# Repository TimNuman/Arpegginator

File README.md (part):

# Arpegginator

Web prototype of a hardware MIDI step sequencer and arpeggiator. The end goal is a standalone device built around a **Teensy 4.1** (ARM Cortex-M7, 600MHz, 1MB RAM) driving a physical grid with RGB LEDs and a reflective memory LCD. This browser version serves as the development environment for the Rust engine -- the same code that runs here as WebAssembly will compile natively for the Teensy.

Place notes on an 8x16 grid, build chords, set up arpeggiation patterns, and send everything out over MIDI to your synths or DAW. The React UI simulates the hardware itself -- an enclosure at true scale carrying the button grid, the panel, the encoders and the transport keys, with host-only controls (tempo, MIDI ports) kept off the case as plain HTML while the Rust engine underneath handles all sequencer state and logic, keeping the path to hardware short.

## Features

### Sequencing

- 6 channels (4 melodic, 2 drum) with 8 patterns each
- Tick-based timing at 480 PPQN with zoom levels from 1/4 to 1/64 notes
- Per-note repeat system with configurable spacing
- Pattern loops with adjustable start point and length
- Pattern queuing with synchronized switching at loop boundaries
- Mute and solo per channel

### Chords and Arpeggios

- Stack notes in scale degrees (thirds, fourths, etc.) to build chords
- Multiple chord voicings per interval/size combination
- Inversions (infinite, up, down)
- Arpeggio styles: up, down, up-down, down-up, or all notes together
- Configurable arp voices (how many chord notes play simultaneously per step)

### Per-Repeat Modulation

Each note has 5 sub-mode arrays that cycle across repeats, each with its own loop behavior (reset, continue, or fill):

- **Velocity** -- per-repeat velocity values
- **Hit chance** -- probability that a repeat fires
- **Timing offset** -- micro-timing nudge as percentage of a step
- **Flam** -- grace note count per repeat
- **Modulate** -- pitch transposition in half steps

### Scales

- Notes are mapped through a configurable scale so the grid always stays in key
- Multiple scale types with root selection by circle of fifths
- Drum channels bypass the scale and map directly to GM MIDI notes

### Sound

- Built-in sounds -- no MIDI hardware needed. Drum channels play an analog-modeled 808 drum synth (kick, snare, clap, hats, toms/congas, cymbals, rimshot/claves, cowbell, maracas, mapped by GM drum note) rendered by the same Rust synth as everything else. Melodic channels play the Rust synth (`arp3-synth`): a polyphonic subtractive engine (selectable waveforms, sub osc, state-variable lowpass, ADSR, glide, drive) compiled to WASM and rendered in an AudioWorklet. Browsers without AudioWorklet fall back to a Web Audio kit and piano (works on e.g. iPad Safari).
- On the Teensy, the _same_ `arp3-synth` crate renders melodic channels through the i.MX RT1062's MQS (Medium Quality Sound) block -- 16-bit 44.1kHz stereo PWM on **pin 10 (right)** and **pin 12 (left)**, driven by a SAI3 FIFO interrupt. Hookup: a first-order RC low-pass per pin (e.g. 1kΩ series + 10nF to ground) into an amp or powered speakers; add a ~10µF DC-blocking cap in series with the output. No codec chip required.
- The Teensy also streams the synth over **USB audio**: the device enumerates as a 44.1kHz 16-bit stereo sound input (same USB audio function as the MIDI interface), so the synth can be monitored or recorded on the computer with no analog wiring at all. The USB stream is a bit-exact tap of what MQS plays.
- **Sound mode** -- per-channel patch editing on the grid (Ctrl + third bottom-row button). The left encoder cycles pages (preset picker, osc 1/2 waveform choosers that draw the wave in LEDs -- Shift+encoder on osc 2 nudges detune -- then amp with vol/mix/sub/glide faders, envelope, filter, FX), the right encoder edits the focused value (Shift for fine), and the grid is directly pressable: fader banks for continuous params, selector rows for waveforms. Edits are audible immediately while the sequencer runs.
- **Presets** -- the first Sound-mode page is a bank of 43 factory patches, color-coded by engine: classic-analog staples (FAT STACK, ACID LINE, RUBBER BASS, STARDUST, HOOVERCRAFT...), NES and SID chip flavors (8-BIT HERO, PIPE DREAM, COIN GET, BREADBIN, SEWER GOBLIN...), 4-op FM sounds (TINE MACHINE, CASTLE BELLS, MECHA BASS, RUST ORGAN...), lo-fi wavetables (OP WON, PHASE DANCER, TAPE GHOST...), additive patches (TONEWHEEL, BELL TOWER, GAMELAN...), and West Coast folder voices (EASEL RIDER, STEEL PAN, FOLD BLOOM, KALIMBA...). Tap a cell or step with the right encoder to load; editing any parameter marks the patch EDITED (amber) and lights a reset cell that restores the preset.
- **Wavefolder** -- a Buchla/Serge-style triangle folder in the shared back end, pre-filter: the FOLD knob (FX page on every engine) drives the signal up to 8x into reflecting boundaries, so harmonics bloom instead of clipping. Identity below unity, so fold 0 is bit-exact clean, and it's a mod-matrix target -- point a WHEEL lane at FOLD for the classic sweep. Drum channels get the same folder per instrument via a FOLD page after the kit chooser -- nine one-column faders (BD, SD, TOM, RS, CP, MA, CB, CY, HH) that draw the kit's fold spectrum on the grid, each press auditioning the drum it folds. Every voice folds against its own envelope, so hits strike folded and decay clean.
- **West Coast engine** -- a fifth synthesis engine built around that folder: a phase-aligned sine-to-triangle core (SHAPE) driven into the fold with adjustable symmetry (SYM offsets into asymmetric folding, DC-blocked) and envelope bloom (BLOOM makes fold depth ride the amp envelope -- strike bright, decay pure, the lowpass-gate gesture). Its FOLD page draws one cycle of the folded core live on the grid (the exact math the DSP runs) with a press-to-jump fold track on the bottom row; WEST holds the fold / shape / sym / bloom faders. The sub oscillator stays clean under the folded core. Presets: EASEL RIDER, STEEL PAN, FOLD BLOOM, WEST BRASS, GOLDEN GATE, KALIMBA (gold in the preset bank).
- **FM engine** -- a second synthesis engine in the style of ALM's Akemie's Castle / the Yamaha YM chips: 4 sine operators, the 8 classic YM2612 algorithms, quantized harmonic ratios (×0.5, ×1..×15), op-1 feedback, and a mod-envelope amount for FM plucks -- through the same sub osc, filter, and drive back end. Loading an FM preset swaps the Sound-mode pages to ALGO (the grid draws the operator routing; bottom row selects algorithms), OP (four ratio faders), and FM (depth / feedback / mod-env / detune faders). The engine follows the preset, so a channel switches engines just by picking a patch.
- **Wavetable engine** -- a third engine in the OP-1's lo-fi digital spirit: a morphing bank of 8 single-cycle tables (sine → triangle → saw → square → pulse → organ → formant → metal), CZ-style phase-distortion warp, and bit-crush with sample-rate decimation. Its WAVE page draws one cycle of the current morphed/warped wave live on the grid (the exact math the DSP runs) with a press-to-jump morph position track on the bottom row; DIGI holds the position / warp / crush / detune faders.
- **Additive engine** -- 16 sine partials with per-harmonic levels and a stretch (inharmonicity) control for bells and gamelan, with automatic muting of partials above Nyquist. Its HARM page turns the grid into a 16-column harmonic editor -- one one-wide fader per partial, draw your spectrum directly on the buttons -- and ADD holds the stretch fader. Presets: TONEWHEEL, GLASS HARP, BELL TOWER, PAN PIPE, BUZZ MACHINE, GAMELAN (rose in the preset bank).
- **808 drum synth** -- an analog-modeled TR-808 kit in the spirit of Tiptop Audio's 808 module line (BD808, SD808, RS808, CP808, MA808, CB808, HH808, CY808 and the tom/conga voices), synthesized in `arp3-synth` from the classic circuit recipes: bridged-T swept sines for kick and toms, dual body sines + snappy noise for the snare, the 6-square Schmitt bank for hats and cymbal (one hi-hat voice, so a closed hat chokes an open one, as on the hardware), the two famous 540/800 Hz squares for the cowbell, and the 3-burst envelope for the clap. Sound mode on a drum channel opens a KIT chooser page followed by one page per instrument -- BD, SD, TOMS, RIM/CLAVE, CLAP, MARACAS, COWBELL, CYMBAL, HI-HAT -- each a fader bank of that module's front-panel knobs (tune / tone / decay / snappy / level, CH+OH decays on the hat page) plus an audition pad in the bottom-right corner (Shift auditions the open hat). Edits stream to the synth live and apply to already-ringing hits.
- **FM drum synth** -- a second kit engine, selectable per channel on the KIT page: a 2-operator phase-modulation kit in the YM-chip / Machinedrum-EFM spirit. Each instrument keeps its page but swaps in an FM knob driving a modulator with its own fast decay -- ratio-1 growl on the kick, an inharmonic x2.43 body on the snare, high-ratio metallic rings for rimshot and cowbell, and a two-stage modulator stack (x5.42 -> x3.52 -> carrier) for the DX-metal cymbal and hats (choke behavior intact). Each kit keeps its own parameter bank, so switching engines never loses knob settings, and a ringing voice finishes on the kit it was struck with.
- **Drum sampler** -- after the instrument pages, the same left-encoder cycle reaches the sampler: 16 sample slots mapped to the GM drum notes (slot 1 = kick 35/36, and so on), so recorded samples replace the 808 recipes note-by-note while empty slots keep the synthesized kit. Five pages: **SLOT** (rows are slots, mirroring the drum lanes -- each loaded row draws its take's waveform across the columns, press a row to select and audition it, Shift+press to snap a pitched sample to the scale root using its auto-detected key), **REC** (arm, record from the browser mic with threshold trigger, pre-roll, and a live scrolling waveform + level meter -- red is reserved for recording), **TRIM** (start/end handles on a press-to-jump track, edits replay the cut), **PLAY** (speed / pitch / level / decay faders, ONE / LOOP / GATE modes, and a GRAIN/TAPE toggle -- granular playback keeps speed and pitch fully independent, TAPE links them as varispeed), and **MOD** (per-slot filter cutoff / resonance / drive). Takes are normalized, key-tagged (YIN pitch detection), and rendered by the same `arp3-synth` crate that will play them from PSRAM on the Teensy, where recording will come from the codec line-in.
- Sends note-on/off to any connected MIDI device via Web MIDI API
- Receives MIDI clock for external sync (start, stop, continue, tempo detection)
- Device selections persist across sessions

### Display

- Simulated **320x240 memory LCD** showing note parameters, chord names, voicings, and playback state -- rendered entirely in Rust and blitted to a canvas via an RGB565 framebuffer, then mapped through a panel simulation so the browser shows what the panel shows. The target panel is a **JDI LPM044M141A**: 4.4", 320x240 over an 89.66 x 67.25 mm active area, reflective, no backlight, and 1 bit per channel. At 0.28 mm per pixel it is coarse enough that the UI is physically large -- a value in Spleen 8x16 stands 2.8 mm tall -- so the design is built for what that panel can show rather than ported onto it.
- **Paper UI** -- white ground, black ink, and no tone in between. There is no grey to dim a label with, so hierarchy comes from size (Spleen 5x8 labels against 8x16 values) and emphasis comes from inversion or a filled slab. Shading is a 4x4 ordered dither, used for areas only -- fader tracks and inactive slots -- never for glyphs or hairlines.
- **Color means live state, never structure.** The only colored pixels on screen are the three modifier buttons along the bottom edge -- blue for the grid, yellow for up/down, magenta for left/right -- plus whichever field the held modifier is currently pointing at, which takes that same color as its well fill. Everything else is black and white. Because color is redundant with the icons and inversion already there, the UI stays complete on a monochrome panel.
- **Bitmap fonts** -- Spleen (BSD-2), parsed straight from BDF at build time into packed 1-bit glyphs. A vector face rasterized at 11px puts stems on fractional coordinates at ~50% coverage, and a 1-bit threshold rounds them away, so `CH` renders as `CII`. Spleen is drawn on the pixel grid, so there is nothing to threshold. The four-size ladder is roughly 12 kB of glyph data against ~175 kB of anti-aliased coverage bytes.
- Color-coded channels on the grid with visual flags for playhead, beat markers, loop boundaries, and selected notes

## Architecture

```
┌─────────────────────────────────────────────────┐
│  React UI (TypeScript)                          │
│  Grid, ButtonGrid, TouchStrip, panel canvas     │
├──────────────┬──────────────────────────────────┤
│  WasmEngine  │  Actions / Playback loop         │
│  (JS<>Rust)  │  (tick scheduling, BPM)          │
├──────────────┴──────────────────────────────────┤
│  Rust Engine (wasm32 / ARM Cortex-M7)           │
│  Pattern storage, playback tick processing,     │
│  grid computation, input handling, OLED         │
├─────────────────────────────────────────────────┤
│  Platform layer (cfg-switched per target)       │
│  WASM: JS callbacks | Teensy: hardware MIDI     │
├─────────────────────────────────────────────────┤
│  Web MIDI API (browser) / USB MIDI (Teensy)     │
└─────────────────────────────────────────────────┘
```

The Rust engine is the single source of truth for all sequencer state. In the browser, React reads grid buffers and UI state directly from WASM linear memory on each render. The JS side owns the transport timer loop (1ms `setTimeout`) and MIDI I/O. On Teensy, the engine runs natively at 600MHz with hardware MIDI output.

### Platform Abstraction

The engine uses `#[cfg(target_arch)]` to switch between platform backends:

- **wasm32** -- calls JS imports via `extern "C"` for MIDI output and UI callbacks
- **arm** -- (planned) direct hardware MIDI and GPIO for Teensy 4.1
- **test** -- no-op stubs for unit testing

### Teensy 4.1 Constraints

The engine is designed to fit within the Teensy's 1MB RAM budget:

- All state lives in fixed-size arrays (no heap allocation required)
- Pool allocators for NoteEvents (1024 slots) and SubModeArrays (512 slots) with graceful degradation on exhaustion
- `f32` only (Cortex-M7 has hardware FPU for single-precision, not double)
- Optimized alpha blending with bitshift instead of division

## Controls

The grid maps to your keyboard like a controller:

```
Row 4:  1 2 3 4 5 6 7 8
Row 5:  Q W E R T Y U I
Row 6:  A S D F G H J K
Row 7:  Z X C V B N M ,
```

Other keys:

- **Space** -- play / stop
- **Arrow keys** -- navigate (with modifiers for mode-specific actions)
- **Backspace** -- deselect / reset
- **Delete** -- delete selected note
- **[ / ]** -- zoom out / in
- **Shift, Ctrl, Alt, Cmd** -- modifier keys for extended actions (shown in the UI)

The grid also responds to mouse clicks and touch input with drag support.

## Prerequisites

- [Node.js](https://nodejs.org/) (v18+)
- [Rust](https://www.rust-lang.org/tools/install) with the `wasm32-unknown-unknown` target (`rustup target add wasm32-unknown-unknown`)
- Any modern browser. Built-in sounds work everywhere; MIDI output/sync additionally requires [Web MIDI API](https://developer.mozilla.org/en-US/docs/Web/API/Web_MIDI_API) support (Chrome, Edge, Opera)

## Getting Started

```bash
# Install dependencies
npm install

# Build the WASM engine (requires Rust + wasm32-unknown-unknown target)
npm run build:wasm

# Start the dev server
npm run dev
```

Open the app and press play -- built-in 808 + piano sounds work out of the box. To drive external gear instead, pick a MIDI output device in the Out selector in the page's top-right corner (Chrome will prompt for MIDI access).

## Build

```bash
# Full production build (WASM + TypeScript + Vite)
npm run build

# WASM only
npm run build:wasm

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
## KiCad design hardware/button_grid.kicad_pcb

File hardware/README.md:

# 16×8 Button Grid PCB

KiCad PCB for the Arpegginator's main button grid: 128 Kailh Choc v1
low-profile switches with per-key RGBW LEDs and anti-ghosting diodes.

## Specs

| Parameter        | Value                                       |
| ---------------- | ------------------------------------------- |
| Grid             | 16 columns × 8 rows (128 keys)              |
| Switch           | Kailh Choc v1 (PG1350), through-hole        |
| LED              | SK6812MINI-E RGBW (3535), addressable chain |
| Anti-ghost diode | 1N4148W (SOD-323), one per switch           |
| Scanning         | 16 column + 8 row GPIO pins (24 total)      |
| LED data         | 1 GPIO pin (serial chain, 128 LEDs)         |
| Key spacing      | 19.05 mm (standard 1U)                      |
| Board size       | ~320 × 172 mm                               |
| Layers           | 2 (F.Cu + B.Cu)                             |

## Matrix Wiring

Each key cell:

```
COL pin ──── SW pad 1 ─┤ switch ├── SW pad 2 ──── Diode anode ─┤►├── Diode cathode ──── ROW pin
```

The 1N4148W diode on each switch prevents ghosting when multiple keys are
pressed simultaneously. Cathode connects to the row line, anode to the switch.

Scanning: drive one column LOW at a time, read all 8 rows. A pressed key
pulls its row LOW through the diode.

## LED Chain

SK6812MINI-E LEDs are daisy-chained in a snaking pattern:

```
Row 0:  LED1 → LED2 → ... → LED16    (left to right)
Row 1:  LED17 ← LED18 ← ... ← LED32  (right to left)
Row 2:  LED33 → LED34 → ... → LED48   (left to right)
  ...etc...
```

This minimizes routing distance for the data line. One GPIO pin (LED_DIN)
drives the entire chain.

## Connectors

- **J1** (20-pin header): COL0–COL15, VCC, GND, LED_DIN, spare
- **J2** (8-pin header): ROW0–ROW7

Both at the bottom edge, 2.54 mm pitch.

## Teensy 4.1 Pin Mapping (suggested)

| Function   | Teensy Pins      | Count |
| ---------- | ---------------- | ----- |
| COL0–COL15 | 0–9, 10–15       | 16    |
| ROW0–ROW7  | 16–17, 20–25     | 8     |
| LED_DIN    | 26 (or any GPIO) | 1     |
| VCC        | 3.3V             | 1     |
| GND        | GND              | 1     |

## Generating the PCB

```bash
python3 generate_pcb.py
```

This writes `button_grid.kicad_pcb` and `bom.md` next to the script. The
script emits a KiCad 10 (format `20260206`) file and then runs
`kicad-cli pcb upgrade --force` on it so the output matches KiCad's exact
canonical serialization — regenerations produce clean, readable diffs
against revisions saved from the KiCad GUI. Requires KiCad 10 with
`kicad-cli` on `PATH` (or installed at the default macOS location); without
it the PCB is still valid but stays in compact form until first opened and
saved in KiCad.

All geometry is parameterized at the top of the script. Adjust `PITCH`,
`MARGIN`, switch footprint offsets, etc. as needed then regenerate.

## Trace Routing (fully routed)

The generated PCB includes complete trace routing (1117 traces, 639 vias):

**F.Cu (front copper):**

- **Column buses**: Vertical trunk at 2.5 mm left of switch center (dodges
  the 3 mm center post), with horizontal stubs to each switch pad 1
- **Switch→diode**: Short vertical trace from switch pad 2 to diode anode

**B.Cu (back copper):**

- **Row buses**: Horizontal traces connecting all 16 diode cathodes per row,
  via at each diode cathode to drop from F.Cu to B.Cu
- **LED data chain**: Horizontal channel at cy−2.0 mm for intra-row
  connections; inter-row connections route through the board margins
  (left for odd→even, right for even→odd transitions)
- **LED VCC bus**: Horizontal power trace (0.5 mm) per row at cy−4.5 mm,
  via at each LED VCC pad with short stub to the bus
- **GND fill**: Full board ground pour, auto-clearance around all other nets

**LED GND**: Via at each LED GND pad connects directly to the B.Cu ground fill.

**Not routed**: Connector fan-out from grid to J1/J2. The column and row buses
are fully connected within the grid, but the last-mile routing to the pin
headers depends on your physical connector choice. Route these manually in KiCad
or replace J1/J2 with direct wiring pads.

## Bill of Materials

| Ref      | Part            | Package | Qty | Notes                   |
| -------- | --------------- | ------- | --- | ----------------------- |
| SW1–128  | Kailh Choc v1   | PG1350  | 128 | Low-profile mech switch |
| D1–128   | 1N4148W         | SOD-323 | 128 | Anti-ghosting diode     |
| LED1–128 | SK6812MINI-E    | 3535    | 128 | RGBW addressable LED    |
| J1       | Pin header 1×20 | 2.54 mm | 1   | Columns + power + LED   |
| J2       | Pin header 1×8  | 2.54 mm | 1   | Rows                    |

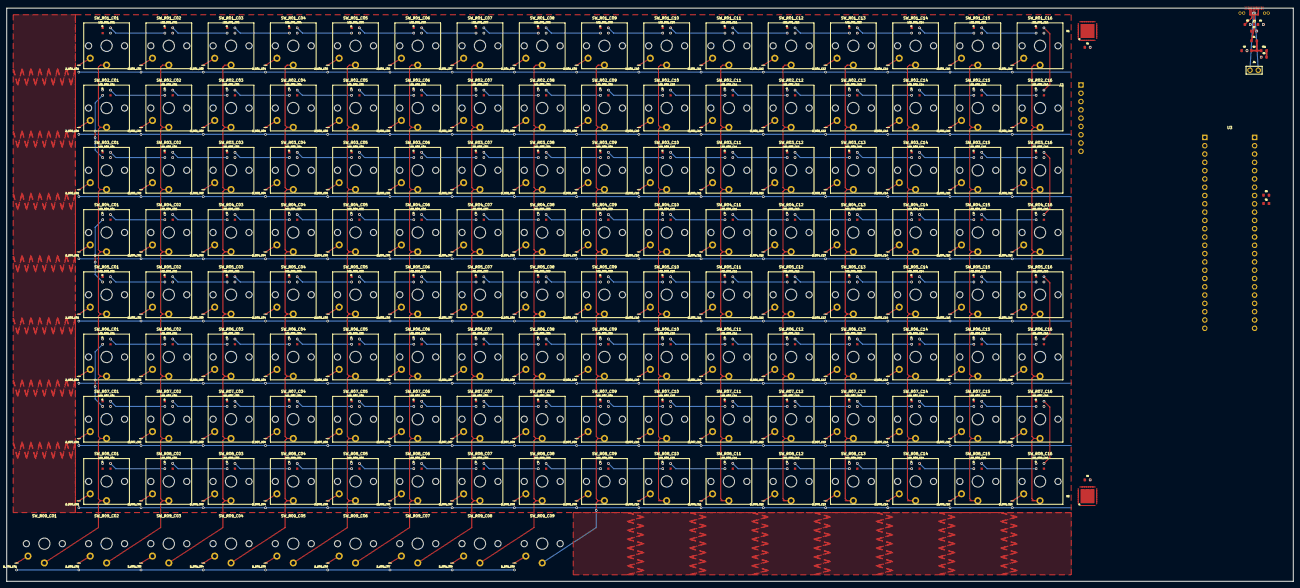
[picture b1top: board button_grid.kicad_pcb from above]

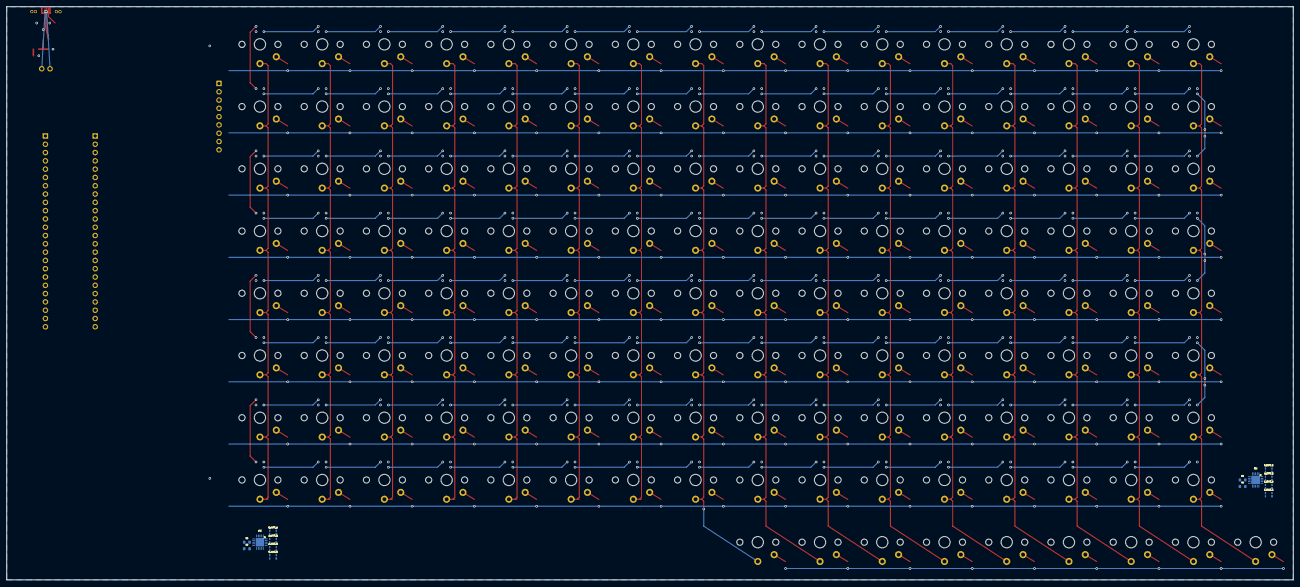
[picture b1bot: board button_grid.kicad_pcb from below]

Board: 2 copper layers, 393.9 x 175.4 mm, 434 parts (14 on the bottom side), 325 nets.

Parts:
C1, C2, C4, C5, C5#2, C6: 100nF; C_0603
C7, C9: 10uF; C_0603
C8: 100uF; C_0603
D_R01_C01, D_R01_C02, D_R01_C03, D_R01_C04, D_R01_C05, D_R01_C06, D_R01_C07, D_R01_C08, D_R01_C09, D_R01_C10, D_R01_C11, D_R01_C12, D_R01_C13, D_R01_C14, D_R01_C15, D_R01_C16, D_R02_C01, D_R02_C02, D_R02_C03, D_R02_C04, D_R02_C05, D_R02_C06, D_R02_C07, D_R02_C08, D_R02_C09, D_R02_C10, D_R02_C11, D_R02_C12, D_R02_C13, D_R02_C14, D_R02_C15, D_R02_C16, D_R03_C01, D_R03_C02, D_R03_C03, D_R03_C04, D_R03_C05, D_R03_C06, D_R03_C07, D_R03_C08, D_R03_C09, D_R03_C10, D_R03_C11, D_R03_C12, D_R03_C13, D_R03_C14, D_R03_C15, D_R03_C16, D_R04_C01, D_R04_C02, D_R04_C03, D_R04_C04, D_R04_C05, D_R04_C06, D_R04_C07, D_R04_C08, D_R04_C09, D_R04_C10, D_R04_C11, D_R04_C12, D_R04_C13, D_R04_C14, D_R04_C15, D_R04_C16, D_R05_C01, D_R05_C02, D_R05_C03, D_R05_C04, D_R05_C05, D_R05_C06, D_R05_C07, D_R05_C08, D_R05_C09, D_R05_C10, D_R05_C11, D_R05_C12, D_R05_C13, D_R05_C14, D_R05_C15, D_R05_C16, D_R06_C01, D_R06_C02, D_R06_C03, D_R06_C04, D_R06_C05, D_R06_C06, D_R06_C07, D_R06_C08, D_R06_C09, D_R06_C10, D_R06_C11, D_R06_C12, D_R06_C13, D_R06_C14, D_R06_C15, D_R06_C16, D_R07_C01, D_R07_C02, D_R07_C03, D_R07_C04, D_R07_C05, D_R07_C06, D_R07_C07, D_R07_C08, D_R07_C09, D_R07_C10, D_R07_C11, D_R07_C12, D_R07_C13, D_R07_C14, D_R07_C15, D_R07_C16, D_R08_C01, D_R08_C02, D_R08_C03, D_R08_C04, D_R08_C05, D_R08_C06, D_R08_C07, D_R08_C08, D_R08_C09, D_R08_C10, D_R08_C11, D_R08_C12, D_R08_C13, D_R08_C14, D_R08_C15, D_R08_C16: 1N4148W; D_SOD-323
D_R09_C01, D_R09_C02, D_R09_C03, D_R09_C04, D_R09_C05, D_R09_C06, D_R09_C07, D_R09_C08, D_R09_C09: D_SOD-323
D_TVS3_0, D_TVS3_1, D_TVS3_2, D_TVS3_3, D_TVS4_0, D_TVS4_1, D_TVS4_2, D_TVS4_3: PRTR5V0U2X; PRTR5V0U2X_SOT-143B
F1: 2A PTC; R_0603
FB1: 600R@100MHz; R_0603
J2: TFT 2.4in; ILI9341_2.4inch
J3: USB-C; USB_C_Mid_Mount
J4: USB D+/D-; USB_Dev_Pads
LED_R01_C01, LED_R01_C02, LED_R01_C03, LED_R01_C04, LED_R01_C05, LED_R01_C06, LED_R01_C07, LED_R01_C08, LED_R01_C09, LED_R01_C10, LED_R01_C11, LED_R01_C12, LED_R01_C13, LED_R01_C14, LED_R01_C15, LED_R01_C16, LED_R02_C01, LED_R02_C02, LED_R02_C03, LED_R02_C04, LED_R02_C05, LED_R02_C06, LED_R02_C07, LED_R02_C08, LED_R02_C09, LED_R02_C10, LED_R02_C11, LED_R02_C12, LED_R02_C13, LED_R02_C14, LED_R02_C15, LED_R02_C16, LED_R03_C01, LED_R03_C02, LED_R03_C03, LED_R03_C04, LED_R03_C05, LED_R03_C06, LED_R03_C07, LED_R03_C08, LED_R03_C09, LED_R03_C10, LED_R03_C11, LED_R03_C12, LED_R03_C13, LED_R03_C14, LED_R03_C15, LED_R03_C16, LED_R04_C01, LED_R04_C02, LED_R04_C03, LED_R04_C04, LED_R04_C05, LED_R04_C06, LED_R04_C07, LED_R04_C08, LED_R04_C09, LED_R04_C10, LED_R04_C11, LED_R04_C12, LED_R04_C13, LED_R04_C14, LED_R04_C15, LED_R04_C16, LED_R05_C01, LED_R05_C02, LED_R05_C03, LED_R05_C04, LED_R05_C05, LED_R05_C06, LED_R05_C07, LED_R05_C08, LED_R05_C09, LED_R05_C10, LED_R05_C11, LED_R05_C12, LED_R05_C13, LED_R05_C14, LED_R05_C15, LED_R05_C16, LED_R06_C01, LED_R06_C02, LED_R06_C03, LED_R06_C04, LED_R06_C05, LED_R06_C06, LED_R06_C07, LED_R06_C08, LED_R06_C09, LED_R06_C10, LED_R06_C11, LED_R06_C12, LED_R06_C13, LED_R06_C14, LED_R06_C15, LED_R06_C16, LED_R07_C01, LED_R07_C02, LED_R07_C03, LED_R07_C04, LED_R07_C05, LED_R07_C06, LED_R07_C07, LED_R07_C08, LED_R07_C09, LED_R07_C10, LED_R07_C11, LED_R07_C12, LED_R07_C13, LED_R07_C14, LED_R07_C15, LED_R07_C16, LED_R08_C01, LED_R08_C02, LED_R08_C03, LED_R08_C04, LED_R08_C05, LED_R08_C06, LED_R08_C07, LED_R08_C08, LED_R08_C09, LED_R08_C10, LED_R08_C11, LED_R08_C12, LED_R08_C13, LED_R08_C14, LED_R08_C15, LED_R08_C16: SK6812MINI-E
R1, R2: 4.7k; R_0603
R3, R4: 5.1k; R_0603
R5: 0R; R_0603
SW_R01_C01, SW_R01_C02, SW_R01_C03, SW_R01_C04, SW_R01_C05, SW_R01_C06, SW_R01_C07, SW_R01_C08, SW_R01_C09, SW_R01_C10, SW_R01_C11, SW_R01_C12, SW_R01_C13, SW_R01_C14, SW_R01_C15, SW_R01_C16, SW_R02_C01, SW_R02_C02, SW_R02_C03, SW_R02_C04, SW_R02_C05, SW_R02_C06, SW_R02_C07, SW_R02_C08, SW_R02_C09, SW_R02_C10, SW_R02_C11, SW_R02_C12, SW_R02_C13, SW_R02_C14, SW_R02_C15, SW_R02_C16, SW_R03_C01, SW_R03_C02, SW_R03_C03, SW_R03_C04, SW_R03_C05, SW_R03_C06, SW_R03_C07, SW_R03_C08, SW_R03_C09, SW_R03_C10, SW_R03_C11, SW_R03_C12, SW_R03_C13, SW_R03_C14, SW_R03_C15, SW_R03_C16, SW_R04_C01, SW_R04_C02, SW_R04_C03, SW_R04_C04, SW_R04_C05, SW_R04_C06, SW_R04_C07, SW_R04_C08, SW_R04_C09, SW_R04_C10, SW_R04_C11, SW_R04_C12, SW_R04_C13, SW_R04_C14, SW_R04_C15, SW_R04_C16, SW_R05_C01, SW_R05_C02, SW_R05_C03, SW_R05_C04, SW_R05_C05, SW_R05_C06, SW_R05_C07, SW_R05_C08, SW_R05_C09, SW_R05_C10, SW_R05_C11, SW_R05_C12, SW_R05_C13, SW_R05_C14, SW_R05_C15, SW_R05_C16, SW_R06_C01, SW_R06_C02, SW_R06_C03, SW_R06_C04, SW_R06_C05, SW_R06_C06, SW_R06_C07, SW_R06_C08, SW_R06_C09, SW_R06_C10, SW_R06_C11, SW_R06_C12, SW_R06_C13, SW_R06_C14, SW_R06_C15, SW_R06_C16, SW_R07_C01, SW_R07_C02, SW_R07_C03, SW_R07_C04, SW_R07_C05, SW_R07_C06, SW_R07_C07, SW_R07_C08, SW_R07_C09, SW_R07_C10, SW_R07_C11, SW_R07_C12, SW_R07_C13, SW_R07_C14, SW_R07_C15, SW_R07_C16, SW_R08_C01, SW_R08_C02, SW_R08_C03, SW_R08_C04, SW_R08_C05, SW_R08_C06, SW_R08_C07, SW_R08_C08, SW_R08_C09, SW_R08_C10, SW_R08_C11, SW_R08_C12, SW_R08_C13, SW_R08_C14, SW_R08_C15, SW_R08_C16: PG1350; Kailh_Choc_V1
SW_R09_C01, SW_R09_C02, SW_R09_C03, SW_R09_C04, SW_R09_C05, SW_R09_C06, SW_R09_C07, SW_R09_C08, SW_R09_C09: Kailh_Choc_V1
U1, U2: MCP23S17; MCP23S17_QFN28
U3: Teensy 4.1; Teensy41
U3#2, U4: MPR121; MPR121_QFN20

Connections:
COL0: SW_R01_C01.1, SW_R02_C01.1, SW_R03_C01.1, SW_R04_C01.1, SW_R05_C01.1, SW_R06_C01.1, SW_R07_C01.1, SW_R08_C01.1, SW_R09_C01.1, U1.21
COL1: SW_R01_C02.1, SW_R02_C02.1, SW_R03_C02.1, SW_R04_C02.1, SW_R05_C02.1, SW_R06_C02.1, SW_R07_C02.1, SW_R08_C02.1, SW_R09_C02.1, U1.22
COL2: SW_R01_C03.1, SW_R02_C03.1, SW_R03_C03.1, SW_R04_C03.1, SW_R05_C03.1, SW_R06_C03.1, SW_R07_C03.1, SW_R08_C03.1, SW_R09_C03.1, U1.23
COL3: SW_R01_C04.1, SW_R02_C04.1, SW_R03_C04.1, SW_R04_C04.1, SW_R05_C04.1, SW_R06_C04.1, SW_R07_C04.1, SW_R08_C04.1, SW_R09_C04.1, U1.24
COL4: SW_R01_C05.1, SW_R02_C05.1, SW_R03_C05.1, SW_R04_C05.1, SW_R05_C05.1, SW_R06_C05.1, SW_R07_C05.1, SW_R08_C05.1, SW_R09_C05.1, U1.25
COL5: SW_R01_C06.1, SW_R02_C06.1, SW_R03_C06.1, SW_R04_C06.1, SW_R05_C06.1, SW_R06_C06.1, SW_R07_C06.1, SW_R08_C06.1, SW_R09_C06.1, U1.26
COL6: SW_R01_C07.1, SW_R02_C07.1, SW_R03_C07.1, SW_R04_C07.1, SW_R05_C07.1, SW_R06_C07.1, SW_R07_C07.1, SW_R08_C07.1, SW_R09_C07.1, U1.27
COL7: SW_R01_C08.1, SW_R02_C08.1, SW_R03_C08.1, SW_R04_C08.1, SW_R05_C08.1, SW_R06_C08.1, SW_R07_C08.1, SW_R08_C08.1, SW_R09_C08.1, U1.28
COL8: SW_R01_C09.1, SW_R02_C09.1, SW_R03_C09.1, SW_R04_C09.1, SW_R05_C09.1, SW_R06_C09.1, SW_R07_C09.1, SW_R08_C09.1, SW_R09_C09.1, U1.1
COL9: SW_R01_C10.1, SW_R02_C10.1, SW_R03_C10.1, SW_R04_C10.1, SW_R05_C10.1, SW_R06_C10.1, SW_R07_C10.1, SW_R08_C10.1, U1.2
COL10: SW_R01_C11.1, SW_R02_C11.1, SW_R03_C11.1, SW_R04_C11.1, SW_R05_C11.1, SW_R06_C11.1, SW_R07_C11.1, SW_R08_C11.1, U1.3
COL11: SW_R01_C12.1, SW_R02_C12.1, SW_R03_C12.1, SW_R04_C12.1, SW_R05_C12.1, SW_R06_C12.1, SW_R07_C12.1, SW_R08_C12.1, U1.4
COL12: SW_R01_C13.1, SW_R02_C13.1, SW_R03_C13.1, SW_R04_C13.1, SW_R05_C13.1, SW_R06_C13.1, SW_R07_C13.1, SW_R08_C13.1, U1.5
COL13: SW_R01_C14.1, SW_R02_C14.1, SW_R03_C14.1, SW_R04_C14.1, SW_R05_C14.1, SW_R06_C14.1, SW_R07_C14.1, SW_R08_C14.1, U1.6
COL14: SW_R01_C15.1, SW_R02_C15.1, SW_R03_C15.1, SW_R04_C15.1, SW_R05_C15.1, SW_R06_C15.1, SW_R07_C15.1, SW_R08_C15.1, U1.7
COL15: SW_R01_C16.1, SW_R02_C16.1, SW_R03_C16.1, SW_R04_C16.1, SW_R05_C16.1, SW_R06_C16.1, SW_R07_C16.1, SW_R08_C16.1, U1.8
DISP_CS: J2.3, U3.L12
DISP_DC: J2.5, U3.L8
DISP_LED: J2.8, U3.L10
DISP_MISO: J2.9, U1.14, U2.14, U3.L14
DISP_MOSI: J2.6, U1.13, U2.13, U3.L13
DISP_RST: J2.4, U3.L9
DISP_SCK: J2.7, U1.12, U2.12, U3.R14
GND: C1.2, C2.2, C4.2, C5.2, C5#2.2, C6.2, C7.2, C8.2, C9.1, D_TVS3_0.1, D_TVS3_1.1, D_TVS3_2.1, D_TVS3_3.1, D_TVS4_0.1, D_TVS4_1.1, D_TVS4_2.1, D_TVS4_3.1, J2.2, J3.A1, J3.A12, J3.SH, LED_R01_C01.3, LED_R01_C02.3, LED_R01_C03.3, LED_R01_C04.3, LED_R01_C05.3, LED_R01_C06.3, LED_R01_C07.3, LED_R01_C08.3, LED_R01_C09.3, LED_R01_C10.3, LED_R01_C11.3, LED_R01_C12.3, LED_R01_C13.3, LED_R01_C14.3, LED_R01_C15.3, LED_R01_C16.3, LED_R02_C01.3, LED_R02_C02.3, LED_R02_C03.3, LED_R02_C04.3, LED_R02_C05.3, LED_R02_C06.3, LED_R02_C07.3, LED_R02_C08.3, LED_R02_C09.3, LED_R02_C10.3, LED_R02_C11.3, LED_R02_C12.3, LED_R02_C13.3, LED_R02_C14.3, LED_R02_C15.3, LED_R02_C16.3, LED_R03_C01.3, LED_R03_C02.3, LED_R03_C03.3, LED_R03_C04.3, LED_R03_C05.3, LED_R03_C06.3, LED_R03_C07.3, LED_R03_C08.3, LED_R03_C09.3, LED_R03_C10.3, LED_R03_C11.3, LED_R03_C12.3, LED_R03_C13.3, LED_R03_C14.3, LED_R03_C15.3, LED_R03_C16.3, LED_R04_C01.3, LED_R04_C02.3, LED_R04_C03.3, LED_R04_C04.3, LED_R04_C05.3, LED_R04_C06.3, LED_R04_C07.3, LED_R04_C08.3, LED_R04_C09.3, LED_R04_C10.3, LED_R04_C11.3, LED_R04_C12.3, LED_R04_C13.3, LED_R04_C14.3, LED_R04_C15.3, LED_R04_C16.3, LED_R05_C01.3, LED_R05_C02.3, LED_R05_C03.3, LED_R05_C04.3, LED_R05_C05.3, LED_R05_C06.3, LED_R05_C07.3, LED_R05_C08.3, LED_R05_C09.3, LED_R05_C10.3, LED_R05_C11.3, LED_R05_C12.3, LED_R05_C13.3, LED_R05_C14.3, LED_R05_C15.3, LED_R05_C16.3, LED_R06_C01.3, LED_R06_C02.3, LED_R06_C03.3, LED_R06_C04.3, LED_R06_C05.3, LED_R06_C06.3, LED_R06_C07.3, LED_R06_C08.3, LED_R06_C09.3, LED_R06_C10.3, LED_R06_C11.3, LED_R06_C12.3, LED_R06_C13.3, LED_R06_C14.3, LED_R06_C15.3, LED_R06_C16.3, LED_R07_C01.3, LED_R07_C02.3, LED_R07_C03.3, LED_R07_C04.3, LED_R07_C05.3, LED_R07_C06.3, LED_R07_C07.3, LED_R07_C08.3, LED_R07_C09.3, LED_R07_C10.3, LED_R07_C11.3, LED_R07_C12.3, LED_R07_C13.3, LED_R07_C14.3, LED_R07_C15.3, LED_R07_C16.3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
HSLIDER0: D_TVS4_0.2, U4.9
HSLIDER1: D_TVS4_0.4, U4.10
HSLIDER2: D_TVS4_1.2, U4.12
HSLIDER3: D_TVS4_1.4, U4.13
HSLIDER4: D_TVS4_2.2, U4.14
HSLIDER5: D_TVS4_2.4, U4.15
HSLIDER6: D_TVS4_3.2, U4.16
HSLIDER7: D_TVS4_3.4, U4.17
I2C_SCL: R2.1, U3.R8, U3#2.4, U4.4
I2C_SDA: R1.1, U3.R9, U3#2.5, U4.5
LED_CH1: LED_R01_C01.2, LED_R01_C02.4
LED_CH2: LED_R01_C02.2, LED_R01_C03.4
LED_CH3: LED_R01_C03.2, LED_R01_C04.4
LED_CH4: LED_R01_C04.2, LED_R01_C05.4
LED_CH5: LED_R01_C05.2, LED_R01_C06.4
LED_CH6: LED_R01_C06.2, LED_R01_C07.4
LED_CH7: LED_R01_C07.2, LED_R01_C08.4
LED_CH8: LED_R01_C08.2, LED_R01_C09.4
LED_CH9: LED_R01_C09.2, LED_R01_C10.4
LED_CH10: LED_R01_C10.2, LED_R01_C11.4
LED_CH11: LED_R01_C11.2, LED_R01_C12.4
LED_CH12: LED_R01_C12.2, LED_R01_C13.4
LED_CH13: LED_R01_C13.2, LED_R01_C14.4
LED_CH14: LED_R01_C14.2, LED_R01_C15.4
LED_CH15: LED_R01_C15.2, LED_R01_C16.4
LED_CH16: LED_R01_C16.2, LED_R02_C16.4
LED_CH17: LED_R02_C15.4, LED_R02_C16.2
LED_CH18: LED_R02_C14.4, LED_R02_C15.2
LED_CH19: LED_R02_C13.4, LED_R02_C14.2
LED_CH20: LED_R02_C12.4, LED_R02_C13.2
LED_CH21: LED_R02_C11.4, LED_R02_C12.2
LED_CH22: LED_R02_C10.4, LED_R02_C11.2
LED_CH23: LED_R02_C09.4, LED_R02_C10.2
LED_CH24: LED_R02_C08.4, LED_R02_C09.2
LED_CH25: LED_R02_C07.4, LED_R02_C08.2
LED_CH26: LED_R02_C06.4, LED_R02_C07.2
LED_CH27: LED_R02_C05.4, LED_R02_C06.2
LED_CH28: LED_R02_C04.4, LED_R02_C05.2
LED_CH29: LED_R02_C03.4, LED_R02_C04.2
LED_CH30: LED_R02_C02.4, LED_R02_C03.2
LED_CH31: LED_R02_C01.4, LED_R02_C02.2
LED_CH32: LED_R02_C01.2, LED_R03_C01.4
LED_CH33: LED_R03_C01.2, LED_R03_C02.4
LED_CH34: LED_R03_C02.2, LED_R03_C03.4
LED_CH35: LED_R03_C03.2, LED_R03_C04.4
LED_CH36: LED_R03_C04.2, LED_R03_C05.4
LED_CH37: LED_R03_C05.2, LED_R03_C06.4
LED_CH38: LED_R03_C06.2, LED_R03_C07.4
LED_CH39: LED_R03_C07.2, LED_R03_C08.4
LED_CH40: LED_R03_C08.2, LED_R03_C09.4
LED_CH41: LED_R03_C09.2, LED_R03_C10.4
LED_CH42: LED_R03_C10.2, LED_R03_C11.4
LED_CH43: LED_R03_C11.2, LED_R03_C12.4
LED_CH44: LED_R03_C12.2, LED_R03_C13.4
LED_CH45: LED_R03_C13.2, LED_R03_C14.4
LED_CH46: LED_R03_C14.2, LED_R03_C15.4
LED_CH47: LED_R03_C15.2, LED_R03_C16.4
LED_CH48: LED_R03_C16.2, LED_R04_C16.4
LED_CH49: LED_R04_C15.4, LED_R04_C16.2
LED_CH50: LED_R04_C14.4, LED_R04_C15.2
LED_CH51: LED_R04_C13.4, LED_R04_C14.2
LED_CH52: LED_R04_C12.4, LED_R04_C13.2
LED_CH53: LED_R04_C11.4, LED_R04_C12.2
LED_CH54: LED_R04_C10.4, LED_R04_C11.2
LED_CH55: LED_R04_C09.4, LED_R04_C10.2
LED_CH56: LED_R04_C08.4, LED_R04_C09.2
LED_CH57: LED_R04_C07.4, LED_R04_C08.2
LED_CH58: LED_R04_C06.4, LED_R04_C07.2
LED_CH59: LED_R04_C05.4, LED_R04_C06.2
LED_CH60: LED_R04_C04.4, LED_R04_C05.2
LED_CH61: LED_R04_C03.4, LED_R04_C04.2
LED_CH62: LED_R04_C02.4, LED_R04_C03.2
LED_CH63: LED_R04_C01.4, LED_R04_C02.2
LED_CH64: LED_R04_C01.2, LED_R05_C01.4
LED_CH65: LED_R05_C01.2, LED_R05_C02.4
LED_CH66: LED_R05_C02.2, LED_R05_C03.4
LED_CH67: LED_R05_C03.2, LED_R05_C04.4
LED_CH68: LED_R05_C04.2, LED_R05_C05.4
LED_CH69: LED_R05_C05.2, LED_R05_C06.4
LED_CH70: LED_R05_C06.2, LED_R05_C07.4
LED_CH71: LED_R05_C07.2, LED_R05_C08.4
LED_CH72: LED_R05_C08.2, LED_R05_C09.4
LED_CH73: LED_R05_C09.2, LED_R05_C10.4
LED_CH74: LED_R05_C10.2, LED_R05_C11.4
LED_CH75: LED_R05_C11.2, LED_R05_C12.4
LED_CH76: LED_R05_C12.2, LED_R05_C13.4
LED_CH77: LED_R05_C13.2, LED_R05_C14.4
LED_CH78: LED_R05_C14.2, LED_R05_C15.4
LED_CH79: LED_R05_C15.2, LED_R05_C16.4
LED_CH80: LED_R05_C16.2, LED_R06_C16.4
LED_CH81: LED_R06_C15.4, LED_R06_C16.2
LED_CH82: LED_R06_C14.4, LED_R06_C15.2
LED_CH83: LED_R06_C13.4, LED_R06_C14.2
LED_CH84: LED_R06_C12.4, LED_R06_C13.2
LED_CH85: LED_R06_C11.4, LED_R06_C12.2
LED_CH86: LED_R06_C10.4, LED_R06_C11.2
LED_CH87: LED_R06_C09.4, LED_R06_C10.2
LED_CH88: LED_R06_C08.4, LED_R06_C09.2
LED_CH89: LED_R06_C07.4, LED_R06_C08.2
LED_CH90: LED_R06_C06.4, LED_R06_C07.2
LED_CH91: LED_R06_C05.4, LED_R06_C06.2
LED_CH92: LED_R06_C04.4, LED_R06_C05.2
LED_CH93: LED_R06_C03.4, LED_R06_C04.2
LED_CH94: LED_R06_C02.4, LED_R06_C03.2
LED_CH95: LED_R06_C01.4, LED_R06_C02.2
LED_CH96: LED_R06_C01.2, LED_R07_C01.4
LED_CH97: LED_R07_C01.2, LED_R07_C02.4
LED_CH98: LED_R07_C02.2, LED_R07_C03.4
LED_CH99: LED_R07_C03.2, LED_R07_C04.4
LED_CH100: LED_R07_C04.2, LED_R07_C05.4
LED_CH101: LED_R07_C05.2, LED_R07_C06.4
LED_CH102: LED_R07_C06.2, LED_R07_C07.4
LED_CH103: LED_R07_C07.2, LED_R07_C08.4
LED_CH104: LED_R07_C08.2, LED_R07_C09.4
LED_CH105: LED_R07_C09.2, LED_R07_C10.4
LED_CH106: LED_R07_C10.2, LED_R07_C11.4
LED_CH107: LED_R07_C11.2, LED_R07_C12.4
LED_CH108: LED_R07_C12.2, LED_R07_C13.4
LED_CH109: LED_R07_C13.2, LED_R07_C14.4
LED_CH110: LED_R07_C14.2, LED_R07_C15.4
LED_CH111: LED_R07_C15.2, LED_R07_C16.4
LED_CH112: LED_R07_C16.2, LED_R08_C16.4
LED_CH113: LED_R08_C15.4, LED_R08_C16.2
LED_CH114: LED_R08_C14.4, LED_R08_C15.2
LED_CH115: LED_R08_C13.4, LED_R08_C14.2
LED_CH116: LED_R08_C12.4, LED_R08_C13.2
LED_CH117: LED_R08_C11.4, LED_R08_C12.2
LED_CH118: LED_R08_C10.4, LED_R08_C11.2
LED_CH119: LED_R08_C09.4, LED_R08_C10.2
LED_CH120: LED_R08_C08.4, LED_R08_C09.2
LED_CH121: LED_R08_C07.4, LED_R08_C08.2
LED_CH122: LED_R08_C06.4, LED_R08_C07.2
LED_CH123: LED_R08_C05.4, LED_R08_C06.2
LED_CH124: LED_R08_C04.4, LED_R08_C05.2
LED_CH125: LED_R08_C03.4, LED_R08_C04.2
LED_CH126: LED_R08_C02.4, LED_R08_C03.2
LED_CH127: LED_R08_C01.4, LED_R08_C02.2
LED_DIN: LED_R01_C01.4, U3.L3
LED_VCC: C8.1, LED_R01_C01.1, LED_R01_C02.1, LED_R01_C03.1, LED_R01_C04.1, LED_R01_C05.1, LED_R01_C06.1, LED_R01_C07.1, LED_R01_C08.1, LED_R01_C09.1, LED_R01_C10.1, LED_R01_C11.1, LED_R01_C12.1, LED_R01_C13.1, LED_R01_C14.1, LED_R01_C15.1, LED_R01_C16.1, LED_R02_C01.1, LED_R02_C02.1, LED_R02_C03.1, LED_R02_C04.1, LED_R02_C05.1, LED_R02_C06.1, LED_R02_C07.1, LED_R02_C08.1, LED_R02_C09.1, LED_R02_C10.1, LED_R02_C11.1, LED_R02_C12.1, LED_R02_C13.1, LED_R02_C14.1, LED_R02_C15.1, LED_R02_C16.1, LED_R03_C01.1, LED_R03_C02.1, LED_R03_C03.1, LED_R03_C04.1, LED_R03_C05.1, LED_R03_C06.1, LED_R03_C07.1, LED_R03_C08.1, LED_R03_C09.1, LED_R03_C10.1, LED_R03_C11.1, LED_R03_C12.1, LED_R03_C13.1, LED_R03_C14.1, LED_R03_C15.1, LED_R03_C16.1, LED_R04_C01.1, LED_R04_C02.1, LED_R04_C03.1, LED_R04_C04.1, LED_R04_C05.1, LED_R04_C06.1, LED_R04_C07.1, LED_R04_C08.1, LED_R04_C09.1, LED_R04_C10.1, LED_R04_C11.1, LED_R04_C12.1, LED_R04_C13.1, LED_R04_C14.1, LED_R04_C15.1, LED_R04_C16.1, LED_R05_C01.1, LED_R05_C02.1, LED_R05_C03.1, LED_R05_C04.1, LED_R05_C05.1, LED_R05_C06.1, LED_R05_C07.1, LED_R05_C08.1, LED_R05_C09.1, LED_R05_C10.1, LED_R05_C11.1, LED_R05_C12.1, LED_R05_C13.1, LED_R05_C14.1, LED_R05_C15.1, LED_R05_C16.1, LED_R06_C01.1, LED_R06_C02.1, LED_R06_C03.1, LED_R06_C04.1, LED_R06_C05.1, LED_R06_C06.1, LED_R06_C07.1, LED_R06_C08.1, LED_R06_C09.1, LED_R06_C10.1, LED_R06_C11.1, LED_R06_C12.1, LED_R06_C13.1, LED_R06_C14.1, LED_R06_C15.1, LED_R06_C16.1, LED_R07_C01.1, LED_R07_C02.1, LED_R07_C03.1, LED_R07_C04.1, LED_R07_C05.1, LED_R07_C06.1, LED_R07_C07.1, LED_R07_C08.1, LED_R07_C09.1, LED_R07_C10.1, LED_R07_C11.1, LED_R07_C12.1, LED_R07_C13.1, LED_R07_C14.1, LED_R07_C15.1, LED_R07_C16.1, LED_R08_C01.1, LED_R08_C02.1, LED_R08_C03.1, LED_R08_C04.1, LED_R08_C05.1, LED_R08_C06.1, LED_R08_C07.1, LED_R08_C08.1, LED_R08_C09.1, LED_R08_C10.1, LED_R08_C11.1, LED_R08_C12.1, LED_R08_C13.1, LED_R08_C14.1, LED_R08_C15.1, LED_R08_C16.1, R5.2
ROW0: D_R01_C01.1, D_R01_C02.1, D_R01_C03.1, D_R01_C04.1, D_R01_C05.1, D_R01_C06.1, D_R01_C07.1, D_R01_C08.1, D_R01_C09.1, D_R01_C10.1, D_R01_C11.1, D_R01_C12.1, D_R01_C13.1, D_R01_C14.1, D_R01_C15.1, D_R01_C16.1, U2.21
ROW1: D_R02_C01.1, D_R02_C02.1, D_R02_C03.1, D_R02_C04.1, D_R02_C05.1, D_R02_C06.1, D_R02_C07.1, D_R02_C08.1, D_R02_C09.1, D_R02_C10.1, D_R02_C11.1, D_R02_C12.1, D_R02_C13.1, D_R02_C14.1, D_R02_C15.1, D_R02_C16.1, U2.22
ROW2: D_R03_C01.1, D_R03_C02.1, D_R03_C03.1, D_R03_C04.1, D_R03_C05.1, D_R03_C06.1, D_R03_C07.1, D_R03_C08.1, D_R03_C09.1, D_R03_C10.1, D_R03_C11.1, D_R03_C12.1, D_R03_C13.1, D_R03_C14.1, D_R03_C15.1, D_R03_C16.1, U2.23
ROW3: D_R04_C01.1, D_R04_C02.1, D_R04_C03.1, D_R04_C04.1, D_R04_C05.1, D_R04_C06.1, D_R04_C07.1, D_R04_C08.1, D_R04_C09.1, D_R04_C10.1, D_R04_C11.1, D_R04_C12.1, D_R04_C13.1, D_R04_C14.1, D_R04_C15.1, D_R04_C16.1, U2.24
ROW4: D_R05_C01.1, D_R05_C02.1, D_R05_C03.1, D_R05_C04.1, D_R05_C05.1, D_R05_C06.1, D_R05_C07.1, D_R05_C08.1, D_R05_C09.1, D_R05_C10.1, D_R05_C11.1, D_R05_C12.1, D_R05_C13.1, D_R05_C14.1, D_R05_C15.1, D_R05_C16.1, U2.25
ROW5: D_R06_C01.1, D_R06_C02.1, D_R06_C03.1, D_R06_C04.1, D_R06_C05.1, D_R06_C06.1, D_R06_C07.1, D_R06_C08.1, D_R06_C09.1, D_R06_C10.1, D_R06_C11.1, D_R06_C12.1, D_R06_C13.1, D_R06_C14.1, D_R06_C15.1, D_R06_C16.1, U2.26
ROW6: D_R07_C01.1, D_R07_C02.1, D_R07_C03.1, D_R07_C04.1, D_R07_C05.1, D_R07_C06.1, D_R07_C07.1, D_R07_C08.1, D_R07_C09.1, D_R07_C10.1, D_R07_C11.1, D_R07_C12.1, D_R07_C13.1, D_R07_C14.1, D_R07_C15.1, D_R07_C16.1, U2.27
ROW7: D_R08_C01.1, D_R08_C02.1, D_R08_C03.1, D_R08_C04.1, D_R08_C05.1, D_R08_C06.1, D_R08_C07.1, D_R08_C08.1, D_R08_C09.1, D_R08_C10.1, D_R08_C11.1, D_R08_C12.1, D_R08_C13.1, D_R08_C14.1, D_R08_C15.1, D_R08_C16.1, U2.28
ROW8: D_R09_C01.1, D_R09_C02.1, D_R09_C03.1, D_R09_C04.1, D_R09_C05.1, D_R09_C06.1, D_R09_C07.1, D_R09_C08.1, D_R09_C09.1
SPI_CS_U1: U1.11, U3.R7
SPI_CS_U2: U2.11, U3.R6
SW_0_0: D_R01_C01.2, SW_R01_C01.2
SW_0_1: D_R01_C02.2, SW_R01_C02.2
SW_0_2: D_R01_C03.2, SW_R01_C03.2
SW_0_3: D_R01_C04.2, SW_R01_C04.2
SW_0_4: D_R01_C05.2, SW_R01_C05.2
SW_0_5: D_R01_C06.2, SW_R01_C06.2
SW_0_6: D_R01_C07.2, SW_R01_C07.2
SW_0_7: D_R01_C08.2, SW_R01_C08.2
SW_0_8: D_R01_C09.2, SW_R01_C09.2
SW_0_9: D_R01_C10.2, SW_R01_C10.2
SW_0_10: D_R01_C11.2, SW_R01_C11.2
SW_0_11: D_R01_C12.2, SW_R01_C12.2
SW_0_12: D_R01_C13.2, SW_R01_C13.2
SW_0_13: D_R01_C14.2, SW_R01_C14.2
SW_0_14: D_R01_C15.2, SW_R01_C15.2
SW_0_15: D_R01_C16.2, SW_R01_C16.2
SW_1_0: D_R02_C01.2, SW_R02_C01.2
SW_1_1: D_R02_C02.2, SW_R02_C02.2
SW_1_2: D_R02_C03.2, SW_R02_C03.2
SW_1_3: D_R02_C04.2, SW_R02_C04.2
SW_1_4: D_R02_C05.2, SW_R02_C05.2
SW_1_5: D_R02_C06.2, SW_R02_C06.2
SW_1_6: D_R02_C07.2, SW_R02_C07.2
SW_1_7: D_R02_C08.2, SW_R02_C08.2
SW_1_8: D_R02_C09.2, SW_R02_C09.2
SW_1_9: D_R02_C10.2, SW_R02_C10.2
SW_1_10: D_R02_C11.2, SW_R02_C11.2
SW_1_11: D_R02_C12.2, SW_R02_C12.2
SW_1_12: D_R02_C13.2, SW_R02_C13.2
SW_1_13: D_R02_C14.2, SW_R02_C14.2
SW_1_14: D_R02_C15.2, SW_R02_C15.2
SW_1_15: D_R02_C16.2, SW_R02_C16.2
SW_2_0: D_R03_C01.2, SW_R03_C01.2
SW_2_1: D_R03_C02.2, SW_R03_C02.2
SW_2_2: D_R03_C03.2, SW_R03_C03.2
SW_2_3: D_R03_C04.2, SW_R03_C04.2
SW_2_4: D_R03_C05.2, SW_R03_C05.2
SW_2_5: D_R03_C06.2, SW_R03_C06.2
SW_2_6: D_R03_C07.2, SW_R03_C07.2
SW_2_7: D_R03_C08.2, SW_R03_C08.2
SW_2_8: D_R03_C09.2, SW_R03_C09.2
SW_2_9: D_R03_C10.2, SW_R03_C10.2
SW_2_10: D_R03_C11.2, SW_R03_C11.2
SW_2_11: D_R03_C12.2, SW_R03_C12.2
SW_2_12: D_R03_C13.2, SW_R03_C13.2
SW_2_13: D_R03_C14.2, SW_R03_C14.2
SW_2_14: D_R03_C15.2, SW_R03_C15.2
SW_2_15: D_R03_C16.2, SW_R03_C16.2
SW_3_0: D_R04_C01.2, SW_R04_C01.2
SW_3_1: D_R04_C02.2, SW_R04_C02.2
SW_3_2: D_R04_C03.2, SW_R04_C03.2
SW_3_3: D_R04_C04.2, SW_R04_C04.2
SW_3_4: D_R04_C05.2, SW_R04_C05.2
SW_3_5: D_R04_C06.2, SW_R04_C06.2
SW_3_6: D_R04_C07.2, SW_R04_C07.2
SW_3_7: D_R04_C08.2, SW_R04_C08.2
SW_3_8: D_R04_C09.2, SW_R04_C09.2
SW_3_9: D_R04_C10.2, SW_R04_C10.2
SW_3_10: D_R04_C11.2, SW_R04_C11.2
SW_3_11: D_R04_C12.2, SW_R04_C12.2
SW_3_12: D_R04_C13.2, SW_R04_C13.2
SW_3_13: D_R04_C14.2, SW_R04_C14.2
SW_3_14: D_R04_C15.2, SW_R04_C15.2
SW_3_15: D_R04_C16.2, SW_R04_C16.2
SW_4_0: D_R05_C01.2, SW_R05_C01.2
SW_4_1: D_R05_C02.2, SW_R05_C02.2
SW_4_2: D_R05_C03.2, SW_R05_C03.2
SW_4_3: D_R05_C04.2, SW_R05_C04.2
SW_4_4: D_R05_C05.2, SW_R05_C05.2
SW_4_5: D_R05_C06.2, SW_R05_C06.2
SW_4_6: D_R05_C07.2, SW_R05_C07.2
SW_4_7: D_R05_C08.2, SW_R05_C08.2
SW_4_8: D_R05_C09.2, SW_R05_C09.2
SW_4_9: D_R05_C10.2, SW_R05_C10.2
SW_4_10: D_R05_C11.2, SW_R05_C11.2
SW_4_11: D_R05_C12.2, SW_R05_C12.2
SW_4_12: D_R05_C13.2, SW_R05_C13.2
SW_4_13: D_R05_C14.2, SW_R05_C14.2
SW_4_14: D_R05_C15.2, SW_R05_C15.2
SW_4_15: D_R05_C16.2, SW_R05_C16.2
SW_5_0: D_R06_C01.2, SW_R06_C01.2
SW_5_1: D_R06_C02.2, SW_R06_C02.2
SW_5_2: D_R06_C03.2, SW_R06_C03.2
SW_5_3: D_R06_C04.2, SW_R06_C04.2
SW_5_4: D_R06_C05.2, SW_R06_C05.2
SW_5_5: D_R06_C06.2, SW_R06_C06.2
SW_5_6: D_R06_C07.2, SW_R06_C07.2
SW_5_7: D_R06_C08.2, SW_R06_C08.2
SW_5_8: D_R06_C09.2, SW_R06_C09.2
SW_5_9: D_R06_C10.2, SW_R06_C10.2
SW_5_10: D_R06_C11.2, SW_R06_C11.2
SW_5_11: D_R06_C12.2, SW_R06_C12.2
SW_5_12: D_R06_C13.2, SW_R06_C13.2
SW_5_13: D_R06_C14.2, SW_R06_C14.2
SW_5_14: D_R06_C15.2, SW_R06_C15.2
SW_5_15: D_R06_C16.2, SW_R06_C16.2
SW_6_0: D_R07_C01.2, SW_R07_C01.2
SW_6_1: D_R07_C02.2, SW_R07_C02.2
SW_6_2: D_R07_C03.2, SW_R07_C03.2
SW_6_3: D_R07_C04.2, SW_R07_C04.2
SW_6_4: D_R07_C05.2, SW_R07_C05.2
SW_6_5: D_R07_C06.2, SW_R07_C06.2
SW_6_6: D_R07_C07.2, SW_R07_C07.2
SW_6_7: D_R07_C08.2, SW_R07_C08.2
SW_6_8: D_R07_C09.2, SW_R07_C09.2
SW_6_9: D_R07_C10.2, SW_R07_C10.2
SW_6_10: D_R07_C11.2, SW_R07_C11.2
SW_6_11: D_R07_C12.2, SW_R07_C12.2
SW_6_12: D_R07_C13.2, SW_R07_C13.2
SW_6_13: D_R07_C14.2, SW_R07_C14.2
SW_6_14: D_R07_C15.2, SW_R07_C15.2
SW_6_15: D_R07_C16.2, SW_R07_C16.2
SW_7_0: D_R08_C01.2, SW_R08_C01.2
SW_7_1: D_R08_C02.2, SW_R08_C02.2
SW_7_2: D_R08_C03.2, SW_R08_C03.2
SW_7_3: D_R08_C04.2, SW_R08_C04.2
SW_7_4: D_R08_C05.2, SW_R08_C05.2
SW_7_5: D_R08_C06.2, SW_R08_C06.2
SW_7_6: D_R08_C07.2, SW_R08_C07.2
SW_7_7: D_R08_C08.2, SW_R08_C08.2
SW_7_8: D_R08_C09.2, SW_R08_C09.2
SW_7_9: D_R08_C10.2, SW_R08_C10.2
SW_7_10: D_R08_C11.2, SW_R08_C11.2
SW_7_11: D_R08_C12.2, SW_R08_C12.2
SW_7_12: D_R08_C13.2, SW_R08_C13.2
SW_7_13: D_R08_C14.2, SW_R08_C14.2
SW_7_14: D_R08_C15.2, SW_R08_C15.2
SW_7_15: D_R08_C16.2, SW_R08_C16.2
SW_R9_0: D_R09_C01.2, SW_R09_C01.2
SW_R9_1: D_R09_C02.2, SW_R09_C02.2
SW_R9_2: D_R09_C03.2, SW_R09_C03.2
SW_R9_3: D_R09_C04.2, SW_R09_C04.2
SW_R9_4: D_R09_C05.2, SW_R09_C05.2
SW_R9_5: D_R09_C06.2, SW_R09_C06.2
SW_R9_6: D_R09_C07.2, SW_R09_C07.2
SW_R9_7: D_R09_C08.2, SW_R09_C08.2
SW_R9_8: D_R09_C09.2, SW_R09_C09.2
USB_CC1: J3.A5, R3.1
USB_D+: J3.A6, J4.1
USB_D-: J3.A7, J4.2
USB_VBUS: C7.1, F1.1, J3.A4, J3.A9
VCC: C1.1, C2.1, C4.1, C5.1, C5#2.1, C6.1, C9.2, D_TVS3_0.3, D_TVS3_1.3, D_TVS3_2.3, D_TVS3_3.3, D_TVS4_0.3, D_TVS4_1.3, D_TVS4_2.3, D_TVS4_3.3, FB1.2, J2.1, R1.2, R2.2, U1.9, U1.18, U2.9, U2.18, U3.L15, U3.R1, U3.R3, U3#2.1, U3#2.20, U4.1, U4.20
VCC_FUSED: F1.2, FB1.1, R5.1
VSLIDER0: D_TVS3_3.4, U3#2.17
VSLIDER1: D_TVS3_3.2, U3#2.16
VSLIDER2: D_TVS3_2.4, U3#2.15
VSLIDER3: D_TVS3_2.2, U3#2.14
VSLIDER4: D_TVS3_1.4, U3#2.13
VSLIDER5: D_TVS3_1.2, U3#2.12
VSLIDER6: D_TVS3_0.4, U3#2.10
VSLIDER7: D_TVS3_0.2, U3#2.9
